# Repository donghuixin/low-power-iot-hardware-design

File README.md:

# low-power-iot-hardware-design

一个面向**低功耗物联网硬件**的 Skill：从需求挖掘到原理图、交互式布局规划、Layout、bring-up 的完整设计与评审流程。但不要过度依赖AI，过于模糊不具备可行性的指令他会拒绝

A Claude and Codex skill for designing and reviewing low-power IoT hardware: requirements elicitation, wireless and part selection, sensor placement, schematic reliability review, power budgeting, an interactive 2D/3D PCB placement planner, PCB layout review, and bring-up.

> **觉得有用？请点右上角 ⭐ Star，或 Fork 一份自己的副本。** 规则、参考资料和布局规划器会持续更新，Star 方便你收到更新，Fork 方便你保存自己的定制并同步上游。欢迎通过 Issue 和 Pull Request 提交改进。

## 使用前必读：这不是一键出板工具

这个 skill 只服务于愿意把设计想清楚、说清楚、并逐步检查结果的人。**布局和布线之前有强制的确认流程**：

| 闸门 | 你需要给出并确认 | 放行后 |
|---|---|---|
| G0 需求与工艺 | 功能与场景、供电与峰值电流、无线、环境、层数、板厚、板厂 | 原理图与选型 |
| G1 机械约束 | 板框尺寸或外壳 DXF、限高、固定孔、每个接口 / 按键 / 灯 / 天线 / 电池贴哪条边、禁布区 | 摆放器件 |
| G2 功能分区 | 每个功能块放哪、信号与电源流向、你看过并认可的布局截图 | 布局检查 |
| G3 布局检查 | `layout_lint.py` 无 P0；你同意保留的问题 | 布线规划 |
| G4 布线规划 | 每层用途、布线优先级（哪些手工、哪些可以工具辅助）、差分对、电源电流、验收分数 | 布线 |
| G5 丝印、位号编号与泪滴 | 20 个出图前的决定逐项回答（丝印工艺与字高、离焊盘距离、位号怎么印、文字方向、极性和 1 脚标记、接口说明、板名版本、订单号位置、编号方式与反标、泪滴策略……）；`finish_lint.py` 无 P0、P1 已改或你同意保留；你看过丝印截图 | 导出 Gerber |
| G6 交付验收 | 布线得分达标且无 P0、DRC 为零、你看过布线截图 | 宣布完成 |

每一级 AI 会把内容和一个确认码发给你，核对无误后回复“确认 G1-xxxxxx”才进入下一级；前面的内容一改，后面的确认自动失效。没放行时，`route_fix.py`、`route_lint.py gate` 和嘉立创 EDA 扩展的写回都会直接拒绝。你只说“帮我把板子布完”，AI 会先逐级提问，不会动手；隔夜自动运行也只会做到下一道闸门为止。

**能力边界：** 布线上只做两件事——检查已有布线（含几何修复），以及按你点名的网络逐批布线（每批不超过 8 个网络，且在已确认的优先级里）。“全局布线”“把整板布完”“剩下的都布了”需要在整板范围内搜索通道，这个 skill 做不了，也会直接拒绝；你可以点名下一批网络，或者自己用 EDA 的自动布线器布普通网络，再回来检查。

为什么这么做：DRC 通过不代表板子能用。只给一句目标、让代理跑一晚上，得到的往往是 DRC 干净、但满是任意角度斜线、长绕线和乱换层的板子——布局错了，布线救不回来。细节和一次真实误用的复盘见 [`references/19-design-gate.md`](references/19-design-gate.md)。

## 它做什么

| 阶段 | 内容 |
|---|---|
| 1. 需求明确 | 把功能描述变成量化指标；主动提出用户没想到的需求（峰值电流、电池末期、OTA、运输模式、认证、产测……）；把需求映射到硬件形态；无线选型按数据率、吞吐、距离、峰值电流、平均功耗比较；传感器放置约束（例如 IMU 是否需要靠近转动中心） |
| 2. 原理图可靠性 | 逐状态检查每个网络：上拉下拉、开漏/推挽/三态、电平域匹配、断电域反灌；驱动电压与驱动电流；睡眠电流逐项清点与峰值电流压降；电源树、充电、保护、去耦与储能；绘制流程与可读性规范（一板一张紧凑原理图、型号规格与注意事项写在图上、近处直连、标准接口用标号、网络命名、文字不重叠、设计意图注释） |
| 2¼. 设计确认与布局检查 | [强制确认流程](references/19-design-gate.md)：需求、外壳与固定件、功能分区、布局检查、布线规划、丝印位号与泪滴、交付验收七道闸门，由用户输入确认码逐级放行；`layout_lint.py` 对照确认内容检查实板布局（固定件位置、分区、禁布区、天线净空、干扰源间距、去耦与晶振负载电容距离） |
| 2½. 交互式布局规划 | [2D/3D 布局规划器](#交互式布局规划器)：摆放主器件，卫星器件自动贴放，实时估计布线复杂度并按规则给出问题，导出结果交回评审 |
| 2¾. 布局布线验证 | [验证器](#布局布线验证器)：电流与回流、EMI 受扰与平面谐振、温度与散热片对比；布线前按概率估计，布线后从 KiCad / Gerber 提取实际铜皮复核 |
| 3. Layout | 叠层与阻抗、布局顺序、天线与射频、电源完整性、信号完整性、晶体、高阻节点、传感器应力与热隔离、EMC/ESD、热、DFM/DFA/DFT；[布线约束与质量评分](#布线约束与质量评分)：八方向几何、线宽线长过孔层约束、自动检查与修复、写入 EDA 前的闸门；布线实操：逐网顺序、升级阶梯、换层与过孔、绕线判据、自动布线器预期（取自 [CADET](https://github.com/LGAI-Research/CADET) 对 283 块开源 2 层板的统计与实测） |
| 4. Bring-up 与量产 | 上电顺序、功耗实测、常见故障排查（睡眠电流大、射频距离短、偶发复位）、认证与产测 |
| 5. 交互式引导 | 根据使用场景分轮追问，把用户确认的目标转成带单位、工况和验收方法的电路指标，并随反馈更新预算。 |
| 6. 设计资料管理 | 按设计问题请用户提供对应型号的数据手册、参考设计或原理图，记录版本与页码，让关键参数可追溯。 |
| 7. EDA 工具接入 | [设计开始时主动引导安装并验证嘉立创 EDA 或 KiCad 的 MCP](references/11-eda-mcp-setup.md)，在 Codex 或 Claude Code 中读取当前工程。 |

每个阶段输出带严重度分级（P0–P3）的问题列表，每条包含位置、后果和修改建议。

**扩展模块：高性能混合信号与医疗手持。** 设计满足任一门槛（持续功耗 >1 W、>50 MHz 或 LVDS、>50 V、FPGA、ADC ≥10 MSPS、接触人体的医疗用途）时自动启用，例如手持超声。启用后按"高压 / 漏电 / 温升 → 电源噪声 → 时钟 → 高速接口"的顺序评审，在原理图冻结前闭合功耗-热、数据率-存储、噪声-纹波、时钟抖动四项预算，并按混合信号顺序 bring-up。内容见 [`references/20`–`25`](references/20-hv-pulser-tr-safety.md) 和清单 E 段。

## 原理图绘制流程

画原理图时按 [`references/09-schematic-readability.md`](references/09-schematic-readability.md) 的十步走：先框图、定一张图的幅面 → 确认符号 → 按手册典型电路列出卫星器件 → 按信号流向摆放、卫星贴所服务的引脚 → 近处直连 → 标准接口与远距离连接用标号 → 整理文字互不重叠 → 把型号、规格和注意事项写在图上 → ERC 清零 → 导出 PDF 通读。默认**一块 PCB 只画一张原理图**，不拆子图，在可读的前提下画得紧凑一些；只有用户要求或 A1 幅面仍放不下时才拆页。下面用 BLE IMU 节点的"主控最小系统"区演示前八步：

## 交互式布局规划器

一个可以离线打开的单文件网页（[`assets/layout-planner.html`](assets/layout-planner.html)，内置示例项目，下载后双击即可试用）。用户只摆核心器件——主控、传感器、天线、连接器、电池和板框；去耦电容、晶体、匹配网络这些小件由算法按最优策略自动贴放。每一步都告诉你这样摆对布线难度有什么影响。

### 单击拾取，卫星跟着环绕

单击托盘或板上的器件把它拿起来，光标由器件本身代替。它的卫星器件——主控周围的去耦电容、晶体及负载电容、射频匹配、DCDC 电感——跟着悬浮起来，沿两条倾斜的轨道环绕。再次单击放下，卫星从轨道飞落，按"离所属引脚最近、不挡出线、远离噪声源"的原则贴到板上最合适的位置。

| 2D | 3D |
|---|---|
|  |  |

摆到差的位置时，右侧立即给出线长、交叉和拥挤的变化与原因；3D 视图里拾取、旋转、放下的操作与 2D 相同。

拾取中按 `R` 或右键旋转 90°，点托盘放回，`Esc` 取消；习惯拖放的话，按住拖动同样可以。

动画默认关闭，卫星静止跟随被拾取的器件。点工具条上的 **✦ 动效** 即可看到上图的环绕、落地回弹和飞落。两种状态都会在放下主件时计算并保存周边件的实际位置。浏览器记住通常的动效偏好。系统启用“减少动态效果”时，页面初始静止，主动点击可在当前页临时播放，刷新后恢复静止。

### 2D 默认，一键切到 3D

默认是 2D 俯视，用 Canvas 绘制、不依赖 WebGL，打开即可交互。工具条正中醒目的 **2D | 3D** 按钮（快捷键 `T`）切到轻量的 3D 视图：右键拖动旋转视角、滚轮缩放、`B` 翻板看背面。Three.js 只在第一次切换时加载，不影响打开速度。两种视图共用同一份数据和交互，在 3D 里也能拾取、旋转、放下。

| 3D 视图 | 3D 中拾取主控 |
|---|---|
|  |  |

### 每一步都有反馈

- **布线复杂度**：总线长、交叉数、拥挤度峰值、关键网络、出线压力、层数建议，每项都有"良好 / 留意 / 需处理"三档和一句含义；点一下指标，画面里高亮对应的器件。规划合格的卫星器件不计入拥挤度，把挤在一起的器件移开，峰值会回落；射频馈线等关键网络按 45° 走线估计长度，"关键网络"一行直接列出超限的是哪几项。
- **本次移动说明原因**：放下或旋转后，器件旁浮起一张小卡片（如"线长 −15.0 mm、交叉 −3"），右侧写明原因，例如"交叉 +2：SPI_IMU 与 VDD 互相穿过"。
- **朝向建议**：选中器件时试算另外三个朝向，明显更好时显示半透明的幽灵朝向，按 `Enter` 采纳。

- **规则检查**：天线贴边与净空区、天线远离电池和连接器、射频馈线长度、IMU 远离板边/螺丝/热源、温湿度隔热、磁力计远离电感、电感远离天线与晶体、去耦与晶体距离、连接器开口朝外等。每条问题带 P0–P3 级别、[核对清单](references/checklists.md)编号和改法，点击即定位，并显示相关的规则区域。

- **拥挤热力图**：哪里走不出线一目了然（2D 为色块，3D 为柱高）。

### 其他细节

- **板框形状可改**：矩形/圆角矩形、胶囊形、倒角矩形、L 形、圆形，以及自定义多边形——在板上拖动顶点改形状，双击边加点、双击顶点删点；改形状后固定孔压到板边会提示。**这里的板框只用于摆放规划，布局完成后建议导出板框 DXF 和位置表，导入嘉立创 EDA 再按外壳图纸绘制最终板框。**
- **开场选定板子尺寸**：先在预设（项目原始尺寸、紧凑、常用、宽松、圆形）或自定义尺寸里选好板框，页面按器件总面积提示是否够大，同时决定固定孔：保留项目中的、四角各放一个 M2，或暂不放置；之后仍可在第 1 步或拖动板边修改。
- **固定孔可增删、可拖动**：第 1 步按 M2/M2.5/M3 添加固定孔，自动放到四角或离板边最近的空位；可以逐个改坐标和孔径，展开第 1 步时在板上直接拖动，双击孔或点 × 删除。离板边、器件或其它孔太近时会提示。
- **八步引导**：板框 → 结构定位件 → 天线 → 受物理约束的传感器 → 主控 → 电源链 → 其余主器件 → 检查与导出；步骤不强制，规则通过时打勾。
- **落点反馈**：合法为青绿，挤占别人的卫星位置或进入天线净空区为琥珀，重叠、出板、压孔为红色并抖动；松手后回到最后一个合法位置。
- **吸附与对齐**：0.5 mm 网格（按住 `Alt` 关闭），贴边器件优先吸到距板边 0.3 mm，与其他器件对齐时显示参考线。
- **不画飞线**：连接关系只参与计算，选中器件时相连器件的轮廓按网络类别着色提亮，画面保持干净。
- **导出**：布局 JSON（交回 Claude 做 Layout 评审）、位置表 CSV（EDA 摆放起点）、板框 DXF（导入嘉立创 EDA 作为初始板框）、2D 快照 PNG。
- 撤销/重做、锁定、方向键微调、动效开关（默认关闭）、深浅主题与阻焊颜色、窄屏抽屉、触屏手势、本地自动保存；画面里只有电路板和器件。

### 怎么用

在对话里让 Claude 帮你规划布局（例如"原理图画完了，帮我规划一下 PCB 上器件怎么摆"）。Claude 会：

1. 按 [`references/12-layout-planner.md`](references/12-layout-planner.md) 从原理图整理出项目数据（板框、主器件外形与引脚组、网络、卫星器件、规则参数）；
2. 运行 `python scripts/make_layout_project.py project.json` 生成该项目专用的页面交给你；
3. 你摆好后从"导出 → 布局 JSON"导出发回，Claude 按 Layout 评审的格式给出意见。
4. 把位置表 CSV 和板框 DXF 导入嘉立创 EDA 作为摆放起点，在其中按外壳图纸绘制最终板框、完成布线（Claude 可通过[嘉立创 EDA 的 MCP](references/11-eda-mcp-setup.md)协助操作）。

指标是启发式估计，用于比较不同摆法，不等于实际布线结果；默认规则参数是典型值，器件手册给出具体数值时在项目数据里覆盖。

## 布局布线验证器

和规划器分开的另一个单文件网页（[`assets/layout-verifier.html`](assets/layout-verifier.html)，内置示例，双击即可试用），专门回答"这样摆、这样布，电流怎么走、会不会互相干扰、热不热"。它在布局之后和布线之后各用一次：

- **布线前（估计）**：读入规划器导出的布局 JSON，按引脚朝向和可走通道做概率估计，告诉你供电和回流大概怎么走、哪里会挤、哪个敏感器件离干扰源太近、热点在哪，用来改摆放、指导布线。
- **布线后（简化求解）**：从 KiCad 的 `.kicad_pcb`，或 Gerber + IPC-D-356 网表（嘉立创 EDA、Altium 等）提取真实铜皮，按电源 / 模拟 / 数字 / 射频分组，只解相关的那部分铜皮，查出瓶颈、压降、过孔电流、射频参考平面缺口、并行耦合和地铜孤岛。

计算在后台 Worker 里做，求解器带多重网格预条件，一次分析在几百毫秒内完成；动效可以关，帧耗时高时自动降级。

工具条上的 **2D | 3D** 按钮（快捷键 `T`）把同一份结果搬到立体视图里：左键拖动旋转、右键平移、滚轮缩放、双击复位。Three.js 只在第一次切换时载入，不影响打开速度；"动效"按钮同样控制 3D 里的动画。下面每项功能左边是 2D、右边是 3D。

### 电流与回流

选一个负载，供电从电源起点流过来（暖色），回流从它的地脚流回去（冷色），粒子越亮电流密度越大。高频负载的回流贴着去程走，地平面有缺口时会看到它绕路；右侧给出回路面积、建议线宽、压降和最近的去耦电容。

| 2D | 3D |
|---|---|
|  |  |

2D 演示切换负载，以及把叠层假设成 2 层后回流从贴着去程变成走线；3D 里板子半透明，下方分开画出地平面，去程光点在板上流、回流光点在地平面上流。

### 电磁：受扰地图与平面谐振

天线、射频线、开关节点、电感、时钟各自向外扩散，叠加成受扰地图，IMU、晶体、模拟网络等敏感对象按"高 / 中 / 低"脉动提示。切到"平面谐振"，看电源/地平面对的各阶模态起伏的振型、节线和频率，接近射频频段或时钟谐波时标出来。

| 受扰地图 · 2D | 受扰地图 · 3D |
|---|---|
|  |  |
| **平面谐振 · 2D** | **平面谐振 · 3D** |
|  |  |

3D 里受扰电平做成起伏的地形，天线处隆起成峰，波纹从干扰源向外扩散；平面谐振是上下起伏的振型曲面，节线固定不动。

### 温度：加散热片前后对比

逐个器件选散热片、改风速、改环境温度、打开密闭外壳，左右分屏对比改动前后，分割线可以拖动，标注直接写出"结温 102 °C → 39 °C"。

| 2D | 3D |
|---|---|
|  |  |

给 0.9 W 的主控逐级加大散热片：2D 拖动分割线对比；3D 里温度做成高度，加了散热器的器件上会长出散热片，热点上方飘起热气。

### 布线后：从实际铜皮复核

下图是一块布完线的板子：射频线下方的地平面开了槽、两侧地孔围栏太稀、模拟线贴着数字线走了 8 mm、顶层有一块没打孔的地铜，四条都被查出来并在板上定位。

### 怎么用

1. 布局摆好后，让 Claude 生成验证页面：`python scripts/make_layout_project.py 布局.json --verifier`。Claude 会先按 [`references/13-layout-verifier.md`](references/13-layout-verifier.md) 在 `verify` 块里填好负载电流和功耗。
2. 布线完成后，提供 `.kicad_pcb`（铺铜已填充）或 Gerber + 板框 + IPC 网表，Claude 用 `python scripts/extract_copper.py ... -o copper-pack.json` 提取铜皮，再加 `--copper copper-pack.json` 生成页面；也可以直接把数据包拖进页面。
3. "导出报告"得到验证报告 JSON，Claude 把其中的结论（规则 VF-01…VF-30，其中 VF-16…30 是布线几何、质量与走线原则）并入 Layout 评审。

所有结果都是简化模型的定性结论，相对比较（改动前后、方案 A 与 B）比绝对数值更可靠；不替代 SI/PI/EMC 仿真和实测。

## 设计规则与板厂工艺

线宽画到多细要加钱？0.2 mm 的孔算不算特殊工艺？`scripts/fab_rules.py` 把这些问题变成一次对照：

- **内置嘉立创工艺档案**（[`assets/fab-profiles/jlcpcb.json`](assets/fab-profiles/jlcpcb.json)，检索日期 2026-11-24）：按线宽、线距、过孔归纳成"经济 / 标准 / 加价 / 极限"四档，另有焊环、孔距、板边距、阻焊桥等下限，以及带日期和来源的价格参考。
- **支持自己的板厂**：把工艺表（CSV、Markdown 表格、xlsx 或键值文本）交给 `import`，中英文参数名和 mil / mm 单位自动识别，没认出来的行会列出来。
- **读取设计**：从 KiCad 的 `.kicad_pro`、`.kicad_pcb` 读出网络类、全局下限和板上实际用到的最小线宽、每种过孔规格。
- **对照**：告诉你板子落在哪个价格档、是哪个参数决定的、把哪个数改到多少就能降一档，以及超出能力或自相矛盾的规则。
- **生成**：按目标档位输出 KiCad 自定义规则和四个网络类的建议表。

```text
$ python scripts/fab_rules.py check demo.kicad_pro demo.kicad_pcb
- 按 4 层、1 oz 铜对照
- 价格档位：加价 — 孔 < 0.3 mm 且外径 ≤ 0.4 mm，或 0.15 mm 孔，下单系统加收费用
- 决定档位的参数：过孔 0.25/0.4（孔径/外径）
- 降档办法：改成不小于 0.2/0.45 可回到「标准」档
```

怎么把规则写好（三层规则、成组的网络类、带范围的特例、严格口径验收等八条做法）见 [`references/15-design-rules-and-process.md`](references/15-design-rules-and-process.md)。工艺和价格会调整，下单前以板厂下单系统的实时报价为准。

## 布线约束与质量评分

DRC 只保证走线合法，不保证有序。任意角度的斜线、锐角、锯齿、斜着出焊盘、底层乱穿切碎地，都是把飞线直接画成铜皮的结果。[`references/16-routing-constraints.md`](references/16-routing-constraints.md) 把“布得整齐、可靠”写成了可检查的约束：

- **约束表**：几何 RTG（线段只走 0/45/90/135°、拐角只用 135°、禁止直角与锐角、最小段长、沿焊盘长轴出线）、线宽 RTW、线长 RTL（绕行率、晶振 ≤ 5 mm、USB 长度差）、过孔 RTV（每网预算、换层回流过孔、禁止盘中孔）、间距 RTS、层 RTY（2 层板底层是地、4 层板地层不走线、地破碎度）。每条带默认值、严重度和出处。
- **检查与评分**：`route_lint.py` 读 `.kicad_pcb` 或铜皮数据包，给出 11 项指标（VF-16…26）和总分，任一 P0 即不通过；结果同时显示在验证器阶段 R。
- **自动修复**：`route_fix.py` 把有问题的走线在原锚点之间重建成八方向折线（肘形、三段式，不行再局部 A*），删掉悬空线头和重叠线段，保持连通关系和间距不变，修不了的标出来交给人。
- **写入闸门**：Claude 通过嘉立创 EDA 或 KiCad 落线时，每批线段先写成 `plan.json` 过 `route_lint.py gate`，有任意角度或锐角就拒绝写入；设计确认 G0–G4 没放行时直接拒绝。

```text
$ python scripts/route_lint.py lint tests/fixtures/route-bad.kicad_pcb
得分 61.0 / 100 · 不通过（有 P0）   任意角度 9、锐角 4、晶振线打过孔、底层长跳线 …
$ python scripts/route_fix.py tests/fixtures/route-bad.kicad_pcb --brief design-brief.json -o fixed.kicad_pcb
已写入 fixed.kicad_pcb：修复 9 段走线，删除 22 条、新增 18 条线段
$ python scripts/route_lint.py lint fixed.kicad_pcb
得分 93.3 / 100   任意角度 0、锐角 0；剩下晶振过孔和底层跳线是拓扑问题，要人决定
```

**布线指导思想**（[`references/18-routing-philosophy.md`](references/18-routing-philosophy.md)）：按功能块边读懂电路、边查证资料（联网或读文件前先征得同意）、边定约束、边布线、边检查；综合 ADI AN-1142《高速 ADC PCB 布局布线技巧》与 TI ZHCAAE6B《电机驱动器电路板布局的最佳实践》——电流走环路、单一完整地加分区、去耦电容与芯片同层不隔过孔、裸露焊盘过孔阵列、开尔文连接、拐角只用 135°、不接受直角、绝不出现随机角度。

**嘉立创 EDA 扩展“布局布线检查助手”**（[`eext/lpiot-layout-routing-check`](eext/lpiot-layout-routing-check)，单独上架扩展广场）：在“确认”页逐级填写并确认设计信息（确认码只能由人输入），按板子的功能把网络梳理成 9 档优先级并逐档确认（板子上只亮这一档的网络），对照确认内容检查布局（固定件、分区、禁布区、天线净空、IMU 应力与热、磁力计、去耦距离，带动画），检查布线并打分，G0–G4 放行后局部修复（只改 P0 拐角，其他走线不动，可撤销）和局部等长补偿，出图前检查丝印、位号和泪滴，接入你自己的大模型；本地桥（MCP / HTTP + 令牌，枢纽 + 转发端）让本机 AI 客户端和 `scripts/eda_bridge.py` 与编辑器联动，拓扑见 [`references/26-eda-link.md`](references/26-eda-link.md)。安装包在 [`release/`](eext/lpiot-layout-routing-check/release)。

**演示视频**（真实板：作者的 nRF5340 / MDBT53 可穿戴主板，6 层 24.5 × 35.3 mm、96 个器件，作者同意公开）：[▶ demo.mp4（1 分 44 秒）](eext/lpiot-layout-routing-check/docs/demo.mp4)

| ① 逐级确认 | ② 布局检查 | ③ 优先级逐档确认 |
|---|---|---|
|  |  |  |
| 每级核对摘要后手动输入确认码 | 磁力计离电感 5.7 mm、天线离 TF 卡座 2.6 mm | 按功能梳理成档，逐档确认 |
| **④ 布线检查与局部修复** | **⑤ 等长补偿** | **⑥ 丝印、位号与泪滴** |
|  |  |  |
| 只改 P0：直角斜切、锐角分支，其他走线不动 | 只在偏短的线上加一小段蛇形线，放不下交给人 | 出图前 20 个决定逐项回答，再检查 |

**能力边界：检查图、改图，不是完全自由的自动布线。** 视频里的每一处改动都是局部的：P0 拐角斜切、偏短网络上的一小段蛇形线；放不下的列为人工处理。

**走线原则**（[`references/17-routing-principles.md`](references/17-routing-principles.md)，检查器 `scripts/route_principles.py`）：

- **关键信号优先**：射频 → 晶振 → 开关回路与高压 → 高速差分 → 时钟 → 模拟 → 电源 → 一般信号 → 地。`route_lint.py order` 按档位给出逐网布线顺序；`lint` 会抓“优先级倒挂”——关键网络因为直连通道被一般信号占了而绕行或打孔。
- **就近**：去耦电容到电源引脚 ≤ 3 mm、地焊盘 0.5 mm 内有地过孔，负载电容贴晶振，ESD 在接口 5 mm 内且串在线上，串阻贴驱动端。
- **差分**：同层、并行、线距一致、对内等长（USB ≤ 0.5 mm、LVDS ≤ 0.13 mm）、过孔成对并排、对内不穿线、对外留间距。
- **隔离**：开关节点、时钟、高速差分不与模拟、晶振、射频同层并行超过 5 mm。

整网自动布线器、全局通道规划和 EDA 写入适配器还没有实现，路线图见 `16-routing-constraints.md` 第 11 节。

## 目录结构

```
SKILL.md                         主流程（触发后加载）
references/
  01-requirements.md             需求维度、隐性需求、需求→硬件形态
  02-wireless-selection.md       BLE / WiFi / Thread / LoRa / 蜂窝选型
  03-sensor-placement.md         IMU、磁力计、温湿度、气压、麦克风、光学、天线的放置
  04-schematic-signals.md        信号与驱动层面
  05-power-architecture.md       电池、稳压、充电、保护、去耦
  06-power-budget.md             静态电流、峰值电流、续航
  07-layout.md                   布局布线
  08-bringup-production.md       可测试性、调试、认证、量产
  09-schematic-readability.md    原理图绘制流程与可读性规范
  10-easyeda-execution.md        嘉立创EDA 实施、器件标准化、资料归档与保存验收
  11-eda-mcp-setup.md            嘉立创 EDA 与 KiCad 的 MCP 安装、连接与排错
  12-layout-planner.md           交互式布局规划器：项目数据、功能、指标与规则、解读导出
  13-layout-verifier.md          布局布线验证器：verify 块、提取铜皮、规则 VF-01…30、解读验证报告
  14-routing-practice.md         布线实操（取自 CADET）：规则与密度基准、逐网顺序、升级阶梯、换层、绕线判据、自动布线器预期
  15-design-rules-and-process.md 设计规则与板厂工艺：写规则的八条做法、嘉立创价格档位、导入自有工艺、对照与生成
  16-routing-constraints.md      布线约束与质量评分：八方向几何、线宽线长过孔层约束、检查器与修复器、写入闸门、AI 布线规程
  17-routing-principles.md       走线原则：布线优先级、就近、差分、隔离及对应检查器
  18-routing-philosophy.md       布线指导思想与工作方法（ADI AN-1142、TI ZHCAAE6B）
  19-design-gate.md              强制确认流程：七道闸门、能力边界、布线优先级逐档确认、AI 规则、确认码、工具强制点、布局检查规则、误用案例复盘
  26-eda-link.md                 本地 AI 与嘉立创 EDA 扩展联动：拓扑、接入方式、高效检查、安全、排错
  27-silkscreen-annotation-teardrop.md  出图前：丝印、位号编号、泪滴的 20 个引导问题、嘉立创工艺下限、SLK / ANN / TDR 规则与改法
  20-hv-pulser-tr-safety.md      扩展：高压脉冲、T/R、高压电源与联锁、间距
  21-ultrasound-afe-clock.md     扩展：超声 AFE、采样与 IQ、时钟抖动
  22-low-noise-power-thermal.md  扩展：持续功耗模型、纹波与开关同步、手持热设计
  23-highspeed-lvds-fpga.md      扩展：LVDS、FPGA 核心板载板、数据率与 Wi-Fi 吞吐
  24-medical-handheld-safety.md  扩展：漏电、隔离、声输出、接触温度、探头头
  25-mixed-signal-bringup.md     扩展：混合信号板分级上电与测试
  checklists.md                  各阶段逐项核对清单
scripts/
  design_gate.py                 强制确认流程：模板、各闸门状态、摘要与确认码、记录确认、阶段放行检查
  layout_lint.py                 实板布局检查（对照设计确认文件）：LAY-01…15 与就近原则
  finish_lint.py                 出图前检查：丝印 SLK-01…13、位号编号 ANN-01…05、泪滴 TDR-00…02
  length_match.py                等长组检查（RTL-07）与局部蛇形补齐（八方向、135° 拐角，放不下交给人）
  epro_import.py                 读嘉立创 EDA 专业版工程包（.epro2）：铜皮数据包 + 丝印、位号、泪滴模型
  eda_bridge.py                  经本地桥与嘉立创 EDA 扩展联动：导出板子、同步设计确认、梳理优先级、交叉核对
  power_budget.py                功耗预算与峰值压降检查
  hw_calc.py                     I2C 上拉、储能电容、分压器、晶体负载电容、续航；抖动、纹波、高压储能、数据率
  make_layout_project.py         校验项目数据，生成布局规划页面或验证页面（--verifier / --copper）
  build_layout_planner.py        把规划器源码构建为单文件
  build_layout_verifier.py       把验证器源码构建为单文件
  extract_copper.py              从 KiCad 或 Gerber + IPC-D-356 提取铜皮，生成铜皮数据包
  fab_rules.py                   读取板厂工艺与设计规则，对照价格档位，生成 KiCad 规则和网络类建议
  route_lint.py                  布线几何检查与评分、写入 EDA 前的闸门、生成布线约束文件
  route_fix.py                   把任意角度、锐角、抖动、斜出焊盘的走线修成八方向折线
  route_principles.py            走线原则检查（就近、差分、优先级倒挂、隔离）与推荐布线顺序
eext/
  lpiot-layout-routing-check/    嘉立创 EDA 扩展“布局布线检查助手”：设计确认、优先级逐档确认、布局检查、布线检查、动画、修复写回（需确认）、AI 接口、本地桥
assets/
  layout-planner.html            布局规划器（单文件，内置示例）
  layout-planner/                规划器源码与 Three.js（MIT）
  layout-project-example.json    规划器示例项目
  layout-verifier.html           布局布线验证器（单文件，内置示例）
  layout-verifier/               验证器源码
  layout-verify-example.json     验证器示例（布局 + verify 块）
  routing/                       布线约束文件的 schema 与示例（lpiot-routing/1.0）
  fab-profiles/jlcpcb.json       嘉立创工艺档案：价格档位、各项下限、价格参考与来源
  requirements-template.md       需求与架构文档模板
  power-budget-example.json      功耗预算配置示例
tests/                           规划器与验证器的单元测试、铜皮提取测试与合成板
docs/images/                     README 配图与动图
docs/record/                     动图的录制脚本（虚拟时钟逐帧截图）与原理图流程演示页
```

## 安装

**推荐：先 Fork，再安装你自己的副本。** 这样你对规则和参考资料的定制有地方保存，也能随时同步上游的更新。

```bash
# 1. 在 GitHub 页面右上角点 Fork，然后克隆你的副本
git clone https://github.com/<你的用户名>/low-power-iot-hardware-design.git \
  ~/.claude/skills/low-power-iot-hardware-design

# 2. 关联上游，以后用 git pull upstream main 获取更新
cd ~/.claude/skills/low-power-iot-hardware-design
git remote add upstream https://github.com/donghuixin/low-power-iot-hardware-design.git
```

只想直接使用的话：

```bash
git clone https://github.com/donghuixin/low-power-iot-hardware-design.git \
  ~/.claude/skills/low-power-iot-hardware-design
```

项目级安装则克隆到项目的 `.claude/skills/` 目录下。

**Claude 应用（claude.ai / 桌面端）**：把本仓库打包成 zip（根目录包含 `SKILL.md`），在应用的 Skills 设置中上传。

## 使用示例

评审和咨询类的问题可以直接问：

- "这是我的 nRF52840 原理图（附 PDF），CR2032 供电，睡眠电流要做到 5 µA 以内，帮我审一下。"
- "板子回来后睡眠电流有 300 µA，预期是 4 µA，附原理图和实测条件，怎么查？"
- "帮我看看这个 2.4 GHz 板载天线的 layout 有没有问题（附板文件和外壳材料）。"

要 AI 参与摆放或布线时，第一条消息就把约束说清楚，例如：

> 做一个腕戴动作记录器，CR2032 供电、BLE 连手机、-10–45 °C。外壳 38 × 30 mm 圆角矩形（DXF 附上），顶面限高 2.5 mm、底面贴电池。USB-C 只用来烧录，放下边中间；按键在右边离上角 8 mm；天线朝上边，上边 6 mm 内不放金属。分区想法：天线和 nRF52 在上半部、电源和充电在左下、IMU 在中间靠下。先按流程逐级确认，再开始摆放。

不要这样用：“帮我把这块板布完。”“布局好了，自动布线吧。”“剩下的网络都布了。”——AI 会先说明它不做全局布线，再按七道闸门逐级提问；布线时请点名这一批网络。

## 脚本

```bash
python scripts/design_gate.py init -o design-brief.json
python scripts/design_gate.py status design-brief.json
python scripts/design_gate.py summary design-brief.json G1
python scripts/design_gate.py confirm design-brief.json G1 --quote "确认 G1-4c09ae"
python scripts/design_gate.py require design-brief.json --stage route
python scripts/layout_lint.py board.kicad_pcb --brief design-brief.json --json layout-lint.json
python scripts/design_gate.py priorities design-brief.json --board board.kicad_pcb --write
python scripts/design_gate.py summary design-brief.json T1
python scripts/design_gate.py scope design-brief.json --nets RF_OUT,RF_ANT
python scripts/design_gate.py ask design-brief.json G5
python scripts/finish_lint.py board.kicad_pcb --brief design-brief.json --bom bom.csv --json finish-lint.json -o 出图前检查.md
python scripts/epro_import.py 工程.epro2 -o board-pack.json --finish finish-model.json
python scripts/route_lint.py lint board-pack.json --constraints constraints.json
python scripts/route_fix.py board.kicad_pcb --brief design-brief.json --local -o fixed.kicad_pcb
python scripts/length_match.py board-pack.json --brief design-brief.json -o matched.json --clearance 0.1
python scripts/eda_bridge.py export -o board-pack.json
python scripts/power_budget.py assets/power-budget-example.json
python scripts/hw_calc.py i2c-pullup --vdd 1.8 --cb-pf 40 --speed 400k
python scripts/hw_calc.py bulk-cap --ipeak-ma 15 --pulse-ms 5 --dv 0.2
python scripts/hw_calc.py divider --vin 4.2 --r1 2e6 --r2 1e6
python scripts/hw_calc.py xtal --cl-pf 9 --cstray-pf 3
python scripts/hw_calc.py jitter --fin-mhz 10 --snr-db 74
python scripts/hw_calc.py hvcap --cel-pf 100 --channels 32 --dv 60 --tr-ns 20 --droop-v 1 --cycles 8 --prf-khz 10
python scripts/make_layout_project.py assets/layout-project-example.json --check
python scripts/make_layout_project.py assets/layout-verify-example.json --verifier
python scripts/fab_rules.py show --layers 4
python scripts/fab_rules.py check board.kicad_pro board.kicad_pcb
python scripts/extract_copper.py board.kicad_pcb --project 布局.json -o copper-pack.json
python scripts/route_lint.py lint board.kicad_pcb -o 布线报告.md
python scripts/route_lint.py order board.kicad_pcb
python scripts/route_fix.py board.kicad_pcb --brief design-brief.json -o board-fixed.kicad_pcb
```

除 `extract_copper.py` 和 `route_fix.py`（需要 numpy、scipy、Pillow；`route_lint.py` 读 `.kicad_pcb` 时也会用到）外只依赖 Python 3 标准库（`fab_rules.py` 导入 xlsx 时需要 openpyxl）。规划器与验证器的单元测试：`node --test tests/*.test.js`（Node 18+，无第三方依赖）；铜皮提取、工艺规则、布线检查修复、确认流程与布局检查：`python -m unittest tests/test_extract_copper.py tests/test_fab_rules.py tests/test_routing.py tests/test_design_gate.py tests/test_eda_bridge.py`。

## 参与改进

- 发现规则或参考资料有误、想补充某类器件的放置规则：提交 [Issue](https://github.com/donghuixin/low-power-iot-hardware-design/issues)。
- 想直接改：Fork 后在分支上修改，提交 Pull Request。规划器改动请附上 `node --test tests/*.test.js` 的结果和截图。
- 喜欢这个项目，请点 ⭐ Star，让更多做低功耗硬件的人看到它。

## 说明

文档中的数值均为典型量级，用于判断方向和发现问题；具体设计请以所选器件的 datasheet、参考设计和硬件设计指南为准，并以实测验证。

## License

[MIT](LICENSE)。布局规划器内置的 Three.js 同为 MIT 许可，见 [`assets/layout-planner/vendor/three.LICENSE`](assets/layout-planner/vendor/three.LICENSE)。

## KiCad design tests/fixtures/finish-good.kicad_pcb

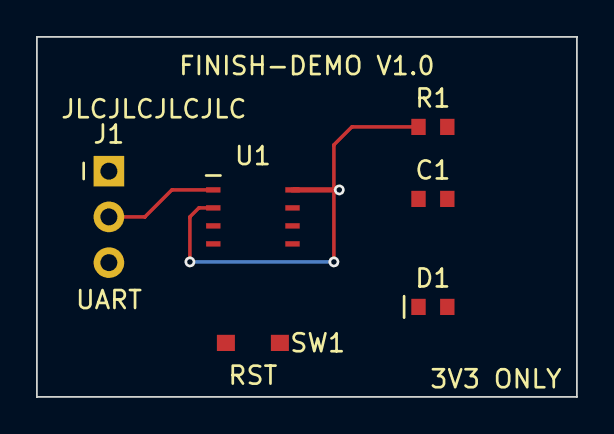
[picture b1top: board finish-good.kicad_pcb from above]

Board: 2 copper layers, 30.0 x 20.0 mm, 6 parts (0 on the bottom side), 6 nets.

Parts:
C1: 100nF; C1
D1: LED red; D1
J1: Header 1x3; J1
R1: 10k; R1
SW1: TS-1187; SW1
U1: STM32G030; U1

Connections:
BTN: SW1.1, U1.3
GND: C1.2, J1.3, SW1.2, U1.4
LED_K: D1.1, U1.6
SIG: R1.1, U1.2
TX: J1.2, U1.1
VDD: C1.1, D1.2, J1.1, R1.2, U1.5

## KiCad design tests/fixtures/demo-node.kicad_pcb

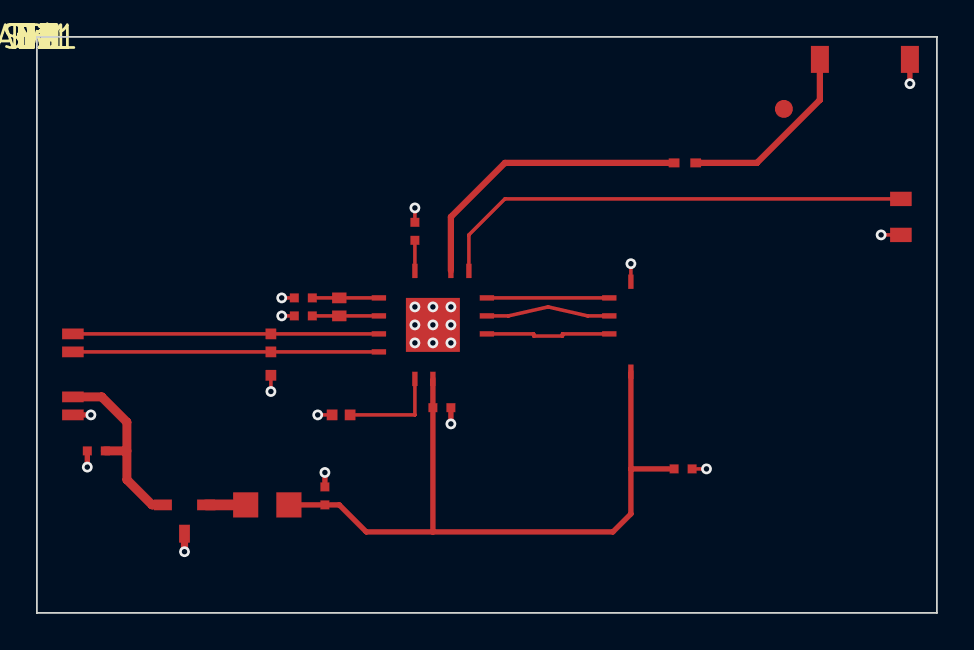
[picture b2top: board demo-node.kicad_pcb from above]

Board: 2 copper layers, 50.0 x 32.0 mm, 19 parts (0 on the bottom side), 16 nets.

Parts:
ANT1: 2.4GHz; ANT1
C1: 100nF; C1
C2: 100nF; C2
C3: 10uF; C3
C4: 12pF; C4
C5: 12pF; C5
C7: 10uF; C7
C8: 100nF; C8
D1: ESD5V; D1
D2: LED; D2
J1: USB-C; J1
L1: 2.2uH; L1
L2: 3.9nH; L2
SW1: KEY; SW1
TP1: TP1
U1: nRF52832; U1
U2: TPS62840; U2
U3: BMI270; U3
Y1: 32MHz; Y1

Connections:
BTN: SW1.1, U1.10
DEC1: C1.1, U1.8
GND: ANT1.2, C1.2, C2.2, C3.2, C4.2, C5.2, C7.2, C8.2, D1.3, D2.2, J1.A1, SW1.2, U1.EP, U2.3, U3.5
INT1: U1.7, U3.3
LED: D2.1, U1.11
RF_ANT: ANT1.1, L2.2
RF_OUT: L2.1, U1.9
SCL: U1.6, U3.2
SDA: U1.5, U3.1
SW: L1.1, U2.2
USB_DM: D1.2, J1.A7, U1.4
USB_DP: D1.1, J1.A6, U1.3
VBUS: C7.1, J1.A4, U2.1
VDD: C2.1, C3.1, C8.1, L1.2, U1.12, U3.4
XIN: C4.1, U1.1, Y1.1
XOUT: C5.1, U1.2, Y1.2

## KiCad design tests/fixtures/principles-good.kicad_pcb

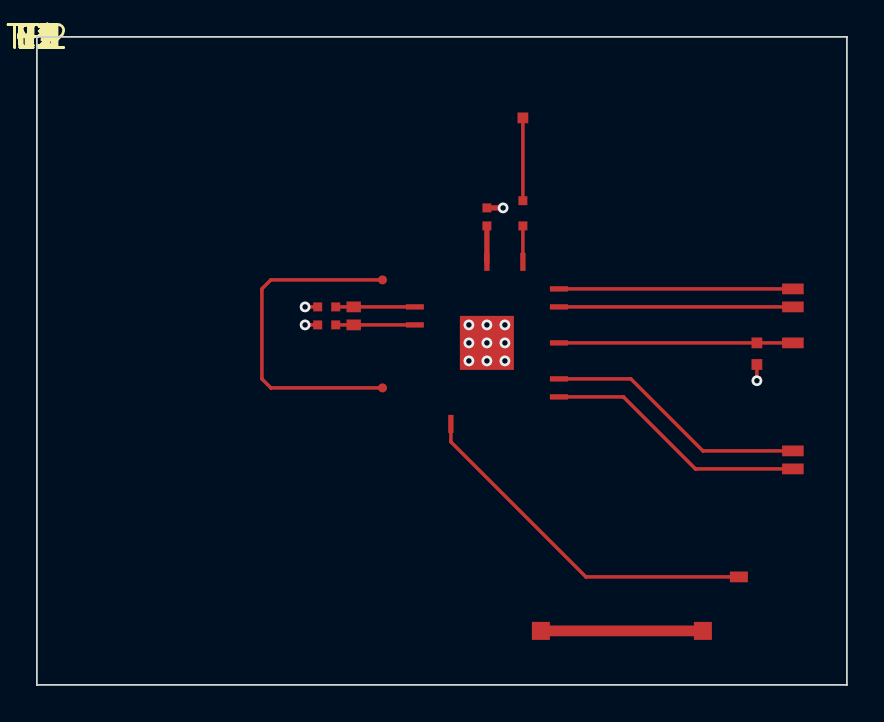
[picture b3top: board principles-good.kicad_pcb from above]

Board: 2 copper layers, 45.0 x 36.0 mm, 15 parts (0 on the bottom side), 14 nets.

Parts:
C1: 100nF; C1
C4: 12pF; C4
C5: 12pF; C5
D1: ESD5V; D1
J1: J1
J2: J2
J3: J3
L1: 2.2uH; L1
R5: 33R; R5
TP1: TP1
TP2: TP2
U1: U1
U2: U2
U3: U3
Y1: 32MHz; Y1

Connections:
ADC_IN: J2.1, U1.9
BTN: D1.1, J1.3, U1.6
GND: C1.2, C4.2, C5.2, D1.2, U1.EP
LED: TP1.1, TP2.1
LVDS_N: J3.2, U1.8
LVDS_P: J3.1, U1.7
SCK: R5.2, U2.1
SCK_R: R5.1, U1.10
SW: L1.1, U3.SW
USB_DM: J1.A7, U1.5
USB_DP: J1.A6, U1.4
VDD: C1.1, U1.1
XIN: C4.1, U1.2, Y1.1
XOUT: C5.1, U1.3, Y1.2

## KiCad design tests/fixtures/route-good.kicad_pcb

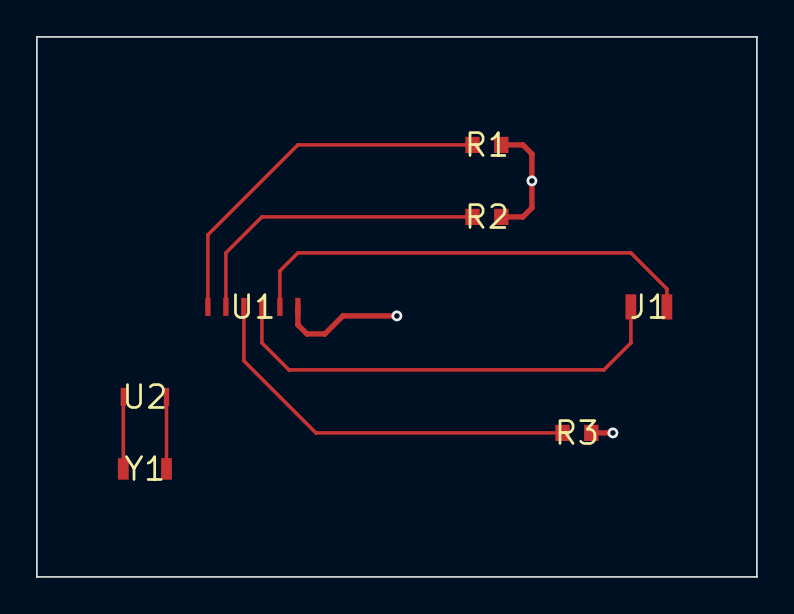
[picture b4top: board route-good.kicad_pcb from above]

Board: 2 copper layers, 40.0 x 30.0 mm, 7 parts (0 on the bottom side), 8 nets.

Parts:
J1: J1
R1: R1
R2: R2
R3: R3
U1: U1
U2: U2
Y1: Y1

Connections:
BTN: J1.2, U1.5
LED: R3.1, U1.3
MISO: J1.1, U1.4
SCL: R2.1, U1.2
SDA: R1.1, U1.1
VDD: R1.2, R2.2, U1.6
XIN: U2.XI, Y1.1
XOUT: U2.XO, Y1.2

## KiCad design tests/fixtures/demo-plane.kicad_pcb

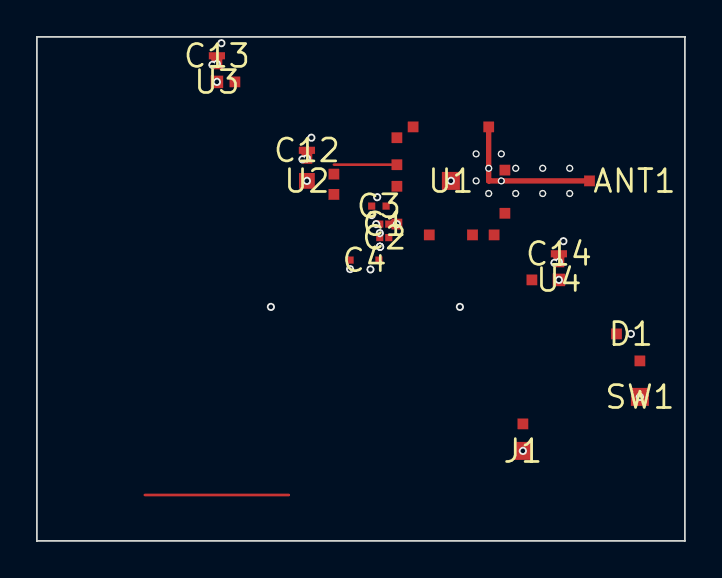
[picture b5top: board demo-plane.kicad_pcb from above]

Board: 4 copper layers, 36.0 x 28.0 mm, 16 parts (1 on the bottom side), 9 nets.

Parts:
ANT1: ANT1
BT1: BT1
C1: C1
C2: C2
C3: C3
C4: C4
C12: C12
C13: C13
C14: C14
D1: D1
J1: J1
SW1: SW1
U1: U1
U2: U2
U3: U3
U4: U4

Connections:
GND: BT1.GND, C1.2, C2.2, C3.2, C4.2, C12.2, C13.2, C14.2, D1.GND, J1.GND, SW1.GND, U1.GND, U2.GND, U3.GND, U4.GND
I2C_ENV: U1.I2C, U3.I2C
IMU_INT: U1.GPIO_A, U2.INT
QSPI_FLASH: U1.QSPI, U4.QSPI
RF_FEED: ANT1.FEED, U1.RF
SPI_IMU: U1.SPI, U2.SPI
SWD: J1.SWD, U1.SWD
UI: D1.A, SW1.A, U1.GPIO_B
VDD: BT1.PLUS, C1.1, C2.1, C3.1, C4.1, C12.1, C13.1, C14.1, U1.VDD, U2.VDD, U3.VDD, U4.VDD
